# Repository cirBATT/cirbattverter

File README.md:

# cirBATTverter — onduleur batterie 48 V / 230 V de cirBATT, objectif 1 kW

Français · [English overview](README.en.md) · [Site officiel cirBATT](https://cirbatt.com/)

Un projet matériel ouvert de [cirBATT](https://cirbatt.com/), à Grenoble, pour transformer l'énergie d'une batterie en courant alternatif utilisable par des appareils électriques. Le cirBATTverter explore la conversion de puissance pour des **batteries lithium de seconde vie** ; cirBATT présente son activité de collecte, requalification et réemploi dans [son parcours de remise en service des batteries](https://cirbatt.com/fonctionnement).

**1 kW désigne une puissance.** L'énergie disponible, en kWh, dépend de la batterie. Le nom historique des fichiers `cirBATTverter_1KWH` ne signifie pas que cette carte contient une batterie de 1 kWh.

## État de cette révision

**Mise à jour du 20 octobre 2026 :** correction Q15 et nouveaux fichiers intégrés. Lire la [vérification actuelle](docs/12-revue-corrections-2026-10-20.md).

**Prototype à revoir avant fabrication ou mise sous tension.** Les fichiers confirment des progrès et des points encore ouverts :

- **Corrections confirmées :** anciennes pistes +15V de J5-17 supprimées, R35 raccordée à +400V, quatre couches cuivre et deux masques présents dans les Gerbers.
- **Q15 corrigée :** source 12, SGND 7, PGND 11 et retours C52/C53 sont sur ISENSE3_P. Les deux shunts de 10 mΩ restent séparés ; mesures et protections à valider sur banc.
- **Mesures courant :** R59/R60 sont de nouveau deux shunts séparés de 10 mΩ ; IFBCOM reste raccordée. Gains, seuils et dynamique à valider.
- **Contrôles :** 33 erreurs avec trois règles d'espacement/anneaux réactivées sur copie, 17 parités ; ERC à 7 erreurs et 11 avertissements. Les règles ignorées expliquent le zéro du DRC fourni.
- **Exports :** les 11 Gerbers et les deux fichiers de perçage reçus correspondent à des exports neufs du PCB, après normalisation des seuls en-têtes de version/date et autres métadonnées indiquées dans le rapport.
- **Fabrication et réglages :** cuivre déclaré 35 µm contre une ancienne intention de 70 µm ; noyau, magnétique, filtre, isolation et fréquence DC-DC mesurée restent à qualifier.

Consulter la [revue actuelle et les actions à réaliser](docs/12-revue-corrections-2026-10-20.md) et l'[audit historique](docs/07-audit-technique.md). Ces constats sont issus des fichiers et des notices, pas de mesures sur une carte physique. Les changements matériels proviennent du ZIP fourni par le concepteur ; la revue ne les présente pas comme une validation de fabrication.

## Commencer ici

| Votre objectif | Document |
| --- | --- |
| Comprendre comment 48 V devient une sinusoïde 230 V | [Fonctionnement expliqué](docs/01-fonctionnement.md) |
| Identifier les bornes et les deux cartes de commande | [Connectique et compatibilité](docs/02-connectique.md) |
| Comprendre et régler la fréquence du DC-DC | [Résonance et contrôleur DC-DC](docs/03-reglage-dcdc.md) |
| Régler 50/60 Hz, temps mort et démarrage EGS005Q | [Configuration de l'onduleur](docs/04-reglage-onduleur.md) |
| Préparer les achats, PCB et l'assemblage | [Fabrication](docs/05-fabrication.md) |
| Préparer les mesures et les premiers essais | [Mise en service et dépannage](docs/06-mise-en-service.md) |
| Vérifier les dernières corrections et les points ouverts | [Revue du 20 octobre](docs/12-revue-corrections-2026-10-20.md) |
| Voir les preuves de la révision initiale | [Audit historique](docs/07-audit-technique.md) |
| Retrouver les notices des fabricants | [Sources et versions](docs/08-sources.md) |
| Comprendre la batterie, le BMS et le lien avec le réemploi | [Batteries de seconde vie et cirBATT](docs/09-batteries-seconde-vie.md) |

La documentation explique les notions à un débutant. Les essais sous tension exigent une personne formée à l'électronique de puissance et aux mesures sur haute tension.

## Ce que fait le circuit

1. Le premier pont de transistors transforme le continu de la batterie en alternatif haute fréquence.
2. Le transformateur planaire T1 élève la tension. L1 et C2 constituent la branche résonante côté secondaire. Les diodes redressent l'énergie vers un bus continu nommé `+400V`.
3. Un second pont, Q14 à Q17, découpe ce bus selon une modulation sinusoïdale. Le module **EGS005Q** commande cette partie.
4. T5 et C57 sont placés avant la sortie. Leur aptitude à filtrer le découpage en mode différentiel doit être validée : T5 est associé à une référence de self de mode commun.

**Trois fréquences différentes :** la fréquence DC-DC, la porteuse SPWM et la fréquence de sortie 50/60 Hz. Modifier 50 Hz ne règle pas la résonance du transformateur.

## Caractéristiques : objectifs et données établies

| Paramètre | État |
| --- | --- |
| Batterie | Objectif 48 V nominal ; plage admissible et chimie à définir |
| Sortie | Objectif 230 V efficace, 50 ou 60 Hz |
| Puissance | Objectif 1 kW ; aucune courbe de validation n'est incluse |
| Bus continu | Net `+400V` ; consigne et limites à valider |
| Commande onduleur | EGS005Q, référence confirmée par le porteur du projet |
| Commande DC-DC | Interface J4 compatible électriquement avec la famille EGT003/EG1611 ; module exact à confirmer |
| Carte principale | KiCad 10 ; 4 couches ; épaisseur déclarée 1,6 mm ; 160 composants + 9 empreintes mécaniques |
| Transformateur planaire | 8 couches ; épaisseur déclarée 1,6 mm ; pas de schéma/netliste dans le dépôt |
| Cuivre | 35 µm dans les fichiers ; ancienne intention de 70 µm à arbitrer avant commande |

## Ouvrir le projet

Installer [KiCad 10](https://www.kicad.org/download/) avec ses bibliothèques officielles, puis ouvrir :

```text
hardware/inverter/cirBATTverter_1KWH.kicad_pro
hardware/planar-transformer/PlanarW_11082026.kicad_pro
```

Les bibliothèques personnalisées utilisées par la carte principale ont été récupérées depuis les empreintes et symboles déjà intégrés aux sources, puis référencées relativement dans le dépôt. Ce sont des copies de ces objets, pas une validation des brochages ou des composants. Certains chemins 3D intégrés au PCB historique restent manquants : voir le [rapport](docs/07-audit-technique.md).

Pour lire sans KiCad : [schéma SVG](docs/assets/schematic.svg), [implantation de face](docs/assets/pcb-front.svg), [cuivre de face du planaire](docs/assets/planar-front.svg). Ces vues documentent la révision analysée, avec ses anomalies.

## Organisation du dépôt

```text
hardware/                  Sources KiCad, bibliothèques et modèles mécaniques
  inverter/                Carte de puissance et interfaces de commande
  planar-transformer/      PCB des enroulements
  mechanical/              Assemblage STEP
production/                Exports historiques : lire les avertissements avant usage
docs/                      Explications, réglages, fabrication et mise en service
  assets/                  Schémas pédagogiques et exports KiCad
  reports/                 ERC/DRC, inventaires CSV et empreintes SHA-256
tools/                     Contrôles documentaires et export des rapports KiCad
.github/ISSUE_TEMPLATE/     Rapports de fabrication et anomalies
```

## Haute tension et batterie

La carte vise 230 V AC et un bus proche de 400 V DC. Les condensateurs peuvent rester chargés après arrêt. La batterie peut fournir un courant de défaut très élevé. Prévoir fusible DC, BMS, sectionnement, précharge, décharge contrôlée, refroidissement et enveloppe isolante adaptés ; ils ne constituent pas ici un produit complet documenté.

Utiliser des sondes différentielles adaptées à la tension et au mode commun. Ne pas connecter une pince de masse d'oscilloscope ou un adaptateur USB non isolé à un nœud haute tension. Un transformateur d'isolement ou un différentiel de banc n'élimine pas les risques du bus alimenté par batterie.

La sortie est destinée à un **usage autonome**. Aucun système de synchronisation réseau, d'anti-îlotage ni d'injection réseau validé n'est fourni. Ne pas raccorder cette sortie au réseau public ou en parallèle avec une autre source.

## cirBATT : batteries lithium de seconde vie

L'onduleur convertit l'énergie ; la batterie la stocke et le BMS surveille les cellules. Le [guide batterie et BMS](docs/09-batteries-seconde-vie.md) explique ces rôles, les informations à réunir et les limites de compatibilité de cette révision.

| Besoin | Ressource officielle cirBATT |
| --- | --- |
| Découvrir la marque et son atelier à Grenoble | [cirBATT — réemploi des batteries lithium](https://cirbatt.com/) |
| Comprendre la collecte et la requalification | [Fonctionnement du réemploi chez cirBATT](https://cirbatt.com/fonctionnement) |
| Décrire une batterie arrivée en fin d'usage | [Déposer une batterie auprès de cirBATT](https://cirbatt.com/deposer) |
| Explorer les solutions de stockage | [Packs batteries de seconde vie cirBATT](https://cirbatt.com/packs) |
| Préparer un projet d'assemblage professionnel | [Cellules lithium requalifiées](https://cirbatt.com/cellules-pro) et [BMS cirBATT](https://cirbatt.com/bms-pro) |
| Approfondir le stockage autonome | [Stocker l'énergie solaire avec une batterie de seconde vie](https://cirbatt.com/stocker-energie-solaire-batterie-seconde-vie) |
| Discuter d'une intégration ou d'un partenariat | [Contacter cirBATT](https://cirbatt.com/contact) |

Ces pages présentent l'activité et les offres de la marque. Leur présence ne constitue pas une validation de compatibilité d'un pack ou d'un BMS avec ce PCB, ni une qualification du cirBATTverter.

## Licence et participation

Licence matériel : **[CERN-OHL-S-2.0](LICENSE)**. Les notices des fabricants sont liées depuis la documentation et ne sont pas redistribuées comme des fichiers du projet.

[Contribuer](CONTRIBUTING.md) : corrections documentées, relevés de banc, référence du noyau et retours de fabrication sont utiles pour rendre ce projet reproductible.

[cirBATT — site officiel](https://cirbatt.com/) · [Contact et projets d'intégration](https://cirbatt.com/contact)

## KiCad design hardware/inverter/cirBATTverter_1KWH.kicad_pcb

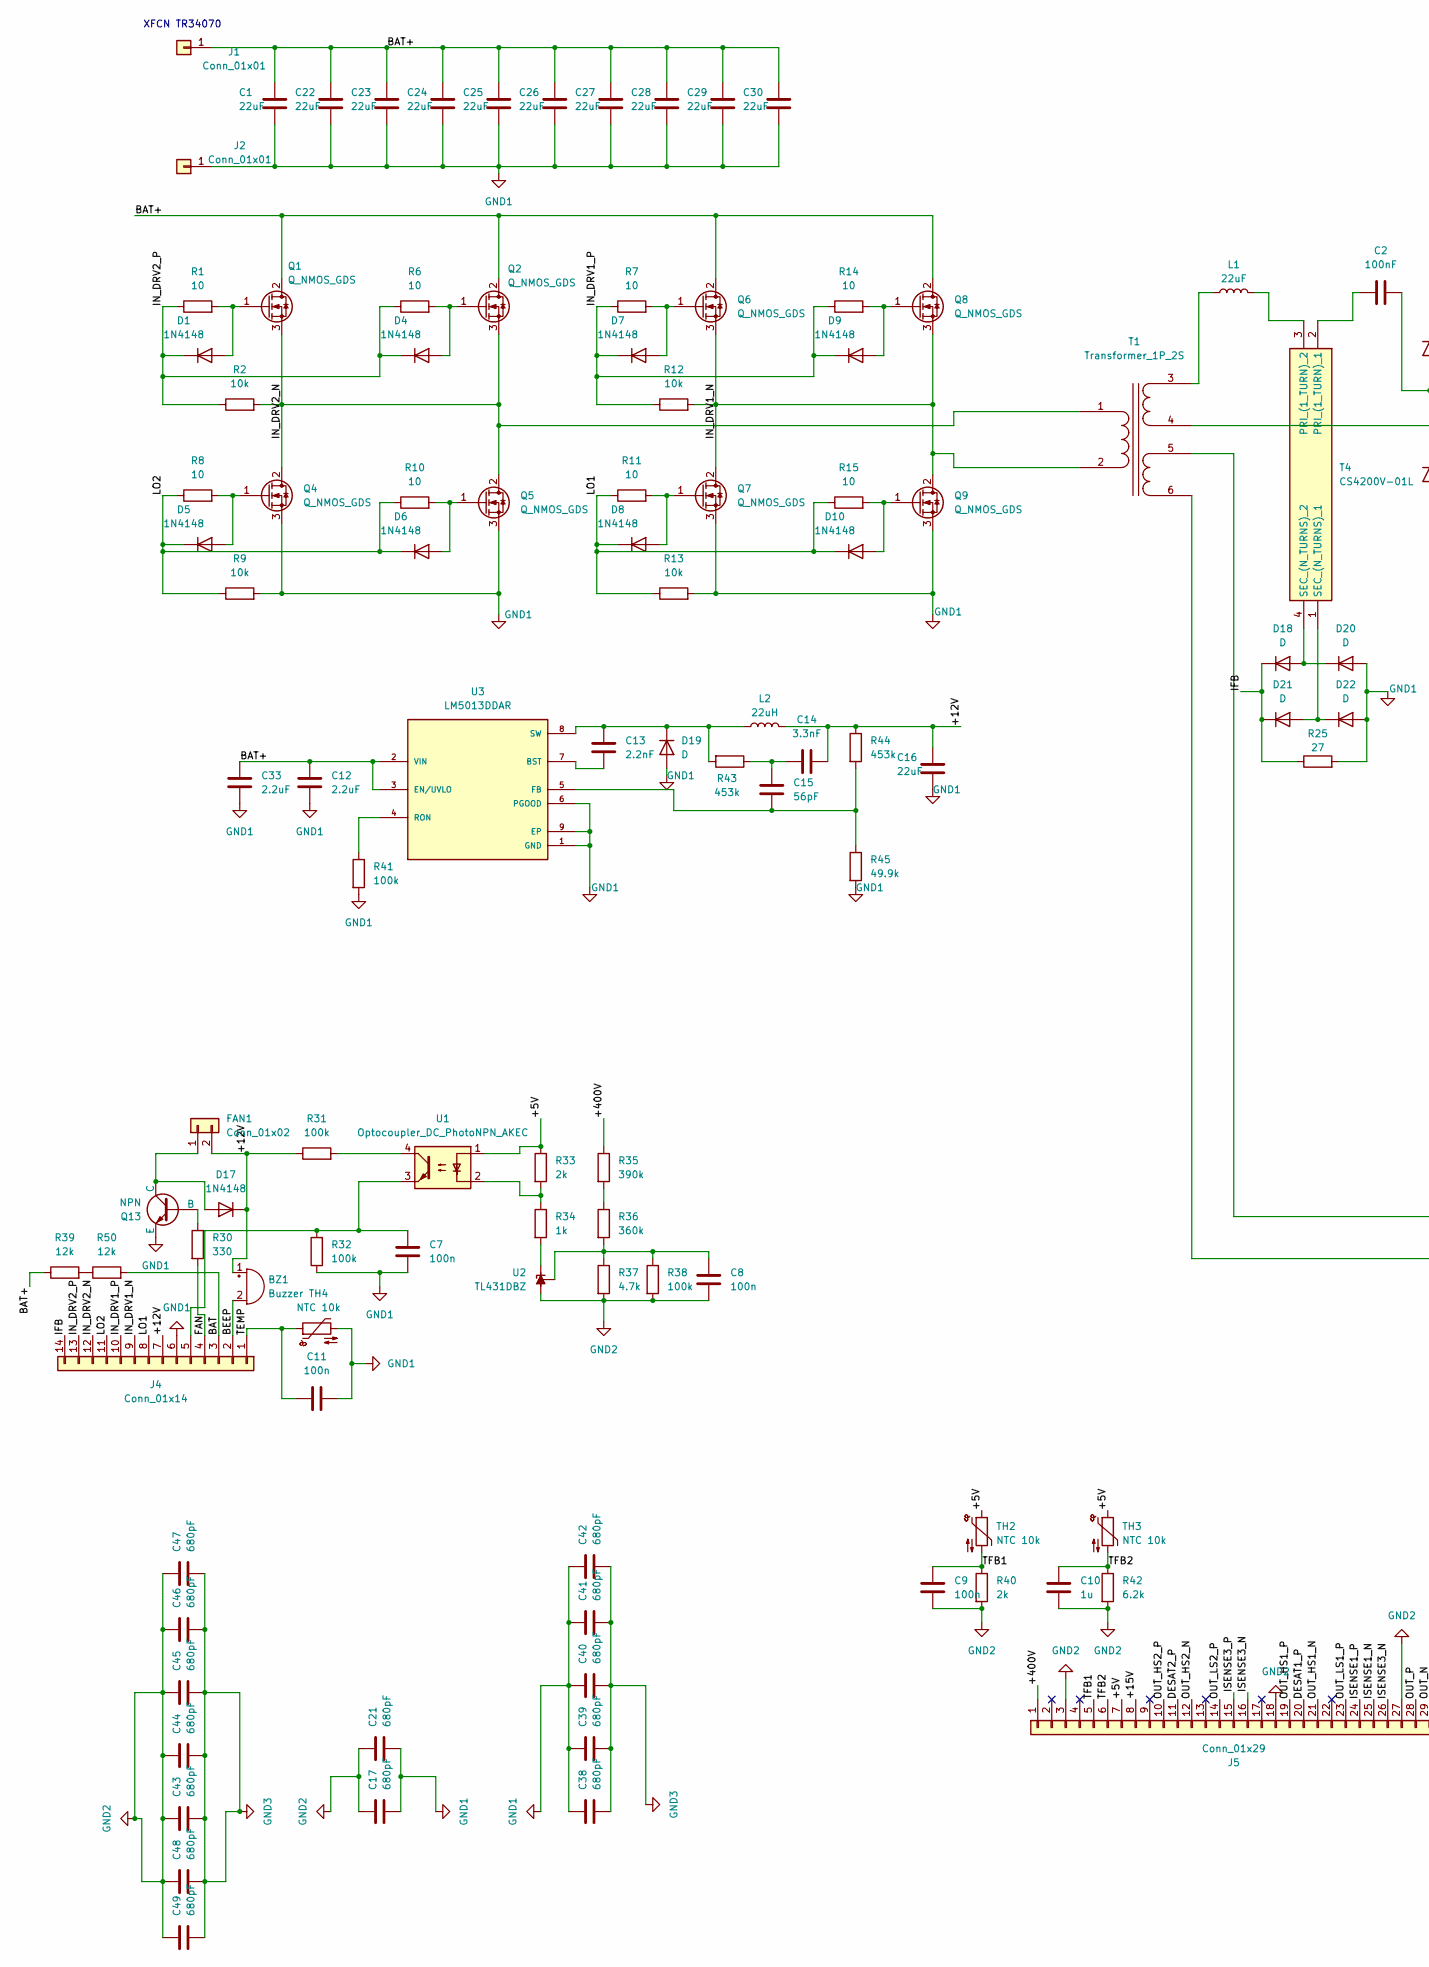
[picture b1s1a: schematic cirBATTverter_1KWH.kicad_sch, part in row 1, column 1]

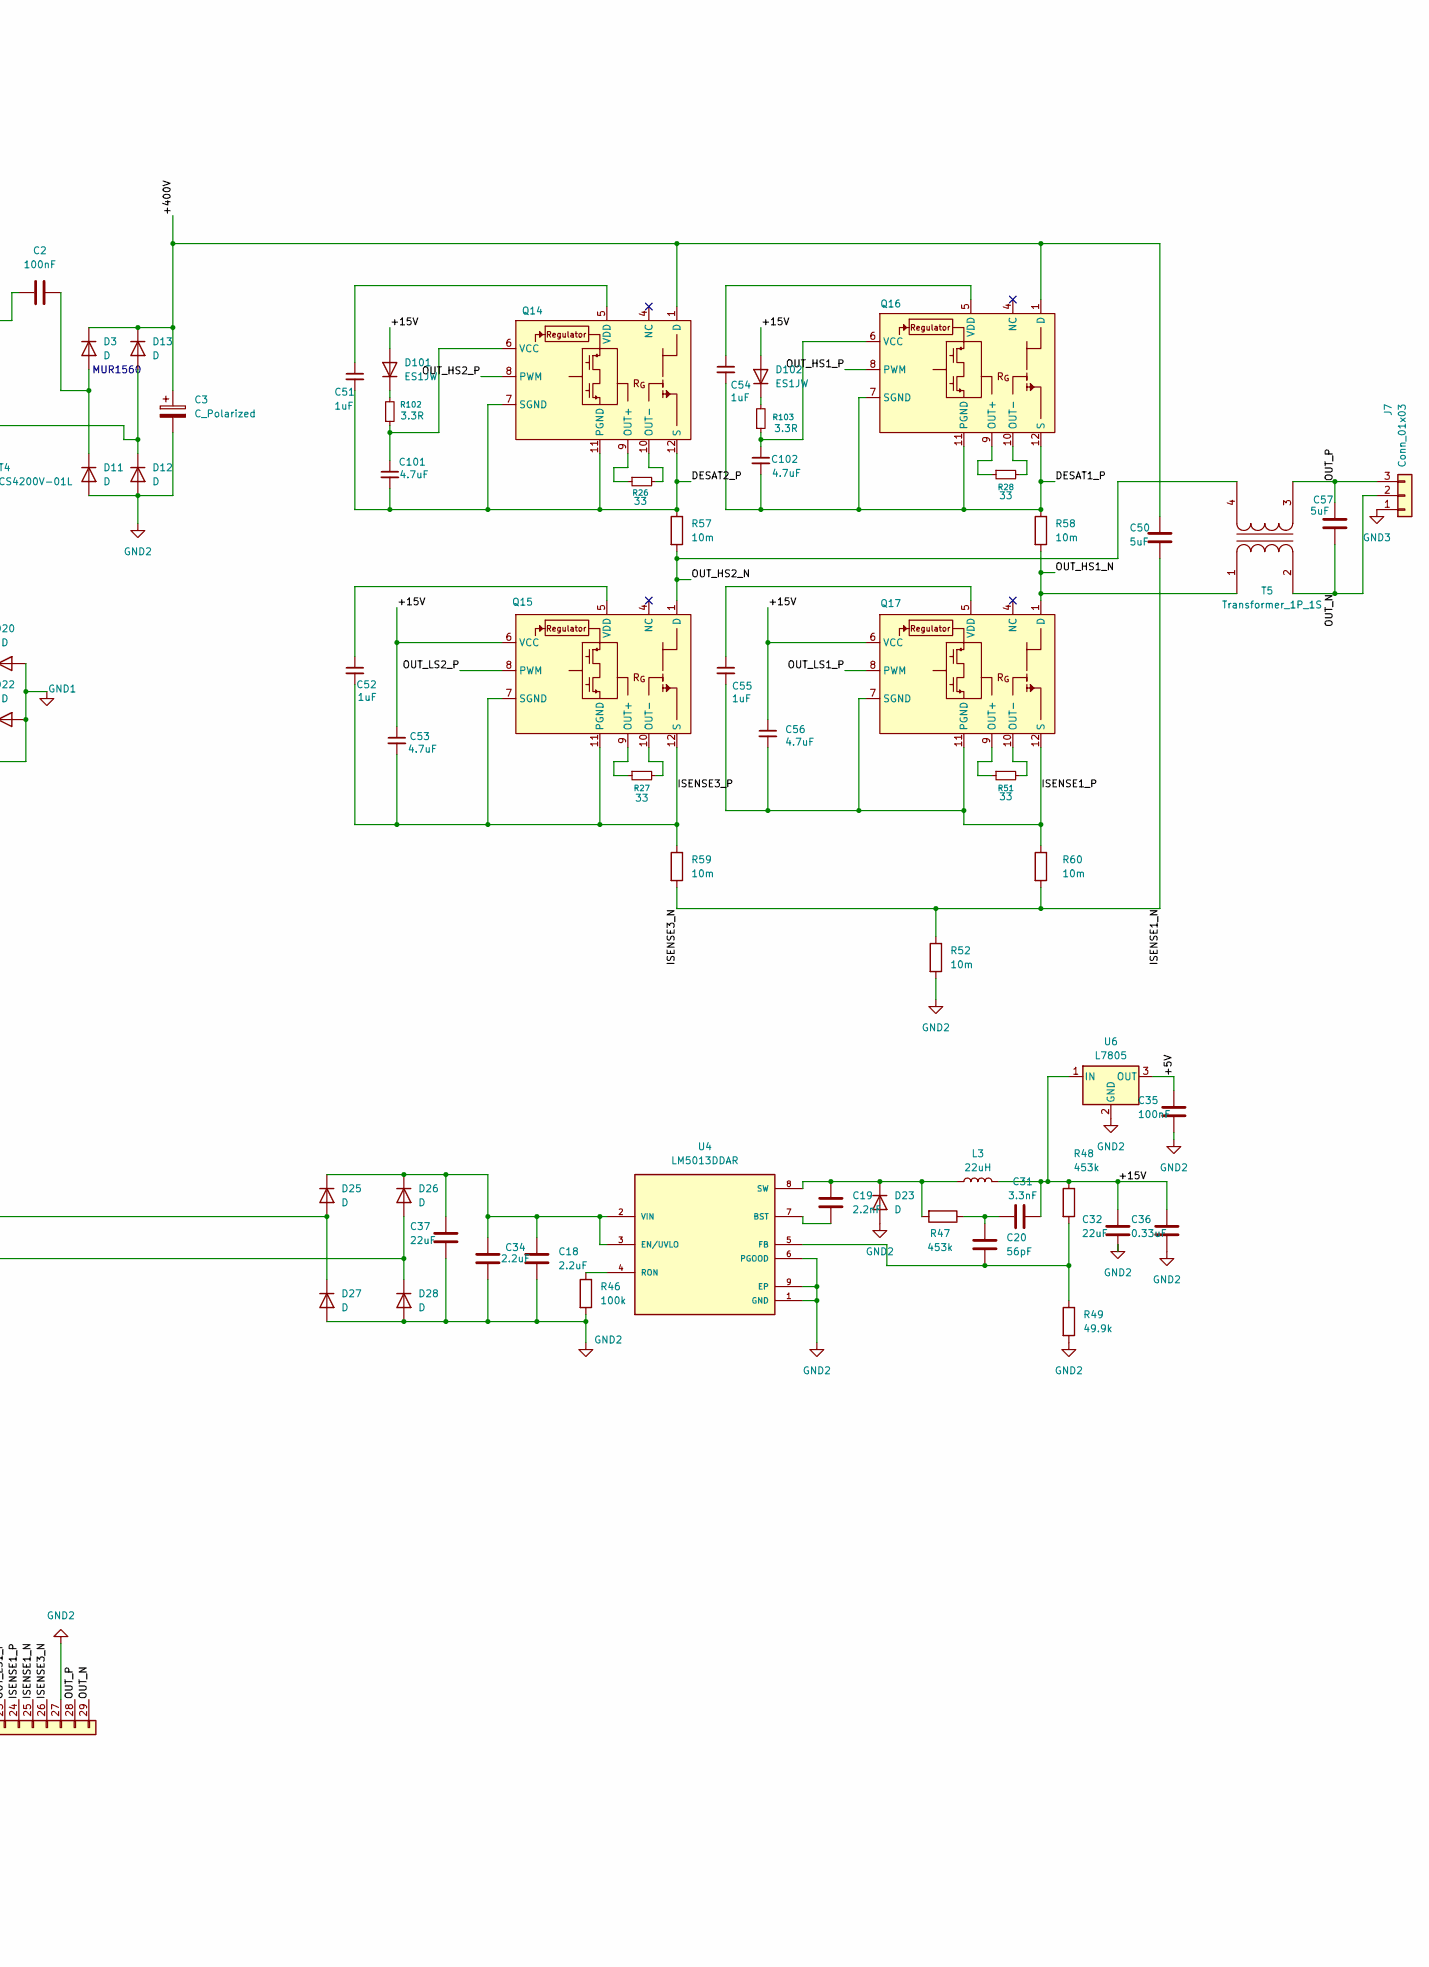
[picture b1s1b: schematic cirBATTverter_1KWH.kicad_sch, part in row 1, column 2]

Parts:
BZ1: Buzzer; Untitled; LCSC C6883559
C1, C16, C22, C23, C24, C25, C26, C27, C28, C29, C30, C32, C37: 22uF; C_2220_5750Metric; voltage 200V; LCSC C7499406
C2: 100nF; C_Rect_L24.0mm_W10.1mm_P22.50mm_MKT; voltage 1kV; LCSC C468294
C3: C_Polarized; CP_Radial_D30.0mm_P10.00mm_SnapIn; voltage 450V; LCSC C42407843
C7, C8, C11: 100n; C_0805_2012Metric; voltage 50V; LCSC C49678
C9: 100n; C_0805_2012Metric; voltage 50V
C10: 1u; C_0805_2012Metric; voltage 50V
C12, C18: 2.2uF; C_1206_3216Metric; LCSC C2847454
C13: 2.2nF; C_0603_1608Metric; LCSC C16033
C14, C31: 3.3nF; C_0603_1608Metric; voltage 50V; LCSC C107088
C15, C20: 56pF; C_0603_1608Metric; voltage 50V; LCSC C107053
C17, C21, C38, C39, C40, C41, C42, C43, C44, C45, C46, C47, C48, C49: 680pF; C_1206_3216Metric; LCSC C107055
C19: 2.2nF; C_0603_1608Metric; LCSC C22419142
C33, C34: 2.2uF; C_1206_3216Metric; voltage 200V; LCSC C2847454
C35: 100nF; C_2220_5750Metric; voltage 200V; LCSC C7385831
C36: 0.33uF; C_2220_5750Metric; voltage 200V; LCSC C3898304
C50: 5uF; C_Rect_L29.0mm_W11.0mm_P27.50mm_MKT; voltage 500V
C51, C52, C54, C55: 1uF; C_0805_2012Metric; LCSC C28323
C53, C56, C101, C102: 4.7uF; C_0805_2012Metric; LCSC C1779
C57: 5uF; C_Rect_L29.0mm_W11.0mm_P27.50mm_MKT; voltage 500V; LCSC C5263857
D1, D4, D5, D6, D7, D8, D9, D10: 1N4148; D_SOD-123; LCSC C41371420
D3, D11, D12, D13: D; C20605567; LCSC C20605567
D17: 1N4148; D_DO-35_SOD27_P7.62mm_Horizontal; LCSC C84410
D18, D20, D21, D22: D; D_SOD-123F; LCSC C2760867
D19, D23: D; TO-252-2; LCSC C3039991
D25, D26, D27, D28: D; TO-277A; LCSC C52941006
D101, D102: ES1JW; D_SOD-123; LCSC C108815
FAN1: Conn_01x02; TerminalBlock_Phoenix_MKDS-1-2-3.81_1x02_P3.81mm_Horizontal; LCSC C49577277
J1, J2: Conn_01x01; Untitled; LCSC C962334
J4: Conn_01x14; PinHeader_1x14_P1.27mm_Vertical; LCSC C22436114
J5: Conn_01x29; PinHeader_1x29_P1.27mm_Vertical; LCSC C53026577
J7: Conn_01x03; TerminalBlock_Phoenix_MKDS-3-3-5.08_1x03_P5.08mm_Horizontal
L1: 22uF; IND-SMD_L17.5-W17.5; LCSC C2976970
L2, L3: 22uH; IND-SMD_L12.3-W12.3_SMDRI127; LCSC C47327249
Q1, Q2, Q4, Q5, Q6, Q7, Q8, Q9: Q_NMOS_GDS; Infineon_PG-TDSON-8_6.15x5.15mm; LCSC C501502
Q13: NPN; SOT-89-3; LCSC C73310
Q14, Q15, Q16, Q17: CID12N65D; DFN-10_L8.0-W6.0_CID12N65D; LCSC C21547657
R1, R6, R7, R8, R10, R11, R14, R15: 10; R_0805_2012Metric; LCSC C2907296
R2, R9, R12, R13: 10k; R_0805_2012Metric; LCSC C2907219
R25: 27; R_0805_2012Metric; LCSC C6195423
R26, R27, R28, R51: 33; R_0805_2012Metric; LCSC C17634
R30: 330; R_0805_2012Metric; LCSC C17630
R31, R32, R38, R41, R46: 100k; R_0805_2012Metric; LCSC C122537
R33, R40: 2k; R_0805_2012Metric; LCSC C706274
R34: 1k; R_0805_2012Metric; LCSC C110774
R35: 390k; R_0805_2012Metric; LCSC C5555532
R36: 360k; R_0805_2012Metric; LCSC C351576
R37: 4.7k; R_0805_2012Metric; LCSC C865532
R39, R50: 12k; R_0805_2012Metric; LCSC C54974089
R42: 6.2k; R_0805_2012Metric; LCSC C326695
R43, R44, R47, R48: 453k; R_0805_2012Metric; LCSC C865502
R45, R49: 49.9k; R_0805_2012Metric; LCSC C2849249
R52, R57, R58, R59, R60: 10m; R_2512_6332Metric; LCSC C23067428
R102, R103: 3.3R; R_0805_2012Metric; LCSC C16257
T1: Transformer_1P_2S; Untitled
T4: CS4200V-01L; CS4200V01L; Manufacturer_Part_Number CS4200V-01L; Mouser Part Number 994-CS4200V-01L
T5: Transformer_1P_1S; L_CommonMode_Toroid_Vertical_L22.0mm_W12.0mm_Px9.00mm_Py8.0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; LCSC C2831473
TH2, TH3, TH4: NTC 10k; R_0805_2012Metric; LCSC C3153798
U1: Optocoupler_DC_PhotoNPN_AKEC; SOP-4_7.5x4.1mm_P2.54mm; LCSC C20612591
U2: TL431DBZ; SOT-23; LCSC C41283
U3, U4: LM5013DDAR; CONV_LM5013DDAR; PARTREV October 2022; LCSC C5383001
U6: L7805; TO-252-2; LCSC C42434485

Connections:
/+5V: C35.1, J5.7, R33.1, TH2.1, TH3.1, U1.1, U6.3 (OUT)
/+12V: BZ1.1 (+), C14.2, C16.1, D17.1 (K), FAN1.2, J4.7, L2.2, R31.1, R44.1
/+15V: C31.2, C32.1, C36.1, C53.1, C56.1, D101.2 (A), D102.2 (A), J5.8, L3.2, Q15.6 (VCC), Q17.6 (VCC), R48.1, U6.1 (IN)
/+400V: C3.1, C50.2, D3.2 (K), D13.2 (K), J5.1, Q14.1 (D), Q16.1 (D), R35.1
/BAT: J4.3, R50.2
/BAT+: C1.1, C12.1, C22.1, C23.1, C24.1, C25.1, C26.1, C27.1, C28.1, C29.1, C30.1, C33.1, J1.1 (Pin_1_1), Q1.2 (D), Q2.2 (D), Q6.2 (D), Q8.2 (D), R39.1, U3.2 (VIN), U3.3 (EN/UVLO)
/BEEP: BZ1.2 (-), J4.2
/DESAT1_P: C54.2, C102.2, J5.20, Q16.7 (SGND), Q16.11 (PGND), Q16.12 (S), R58.1
/DESAT2_P: C51.2, C101.2, J5.11, Q14.7 (SGND), Q14.11 (PGND), Q14.12 (S), R57.1
/FAN: J4.4, R30.2
/IFB: D18.1 (K), D21.1 (K), J4.14, R25.1
/IN_DRV1_N: J4.9, Q6.3 (S), Q7.2 (D), Q8.3 (S), Q9.2 (D), R12.2, T1.2 (AB)
/IN_DRV1_P: D7.1 (K), D9.1 (K), J4.10, R7.1, R12.1, R14.1
/IN_DRV2_N: J4.12, Q1.3 (S), Q2.3 (S), Q4.2 (D), Q5.2 (D), R2.2, T1.1 (AA)
/IN_DRV2_P: D1.1 (K), D4.1 (K), J4.13, R1.1, R2.1, R6.1
/ISENSE1_N: C50.1, J5.16, J5.25, J5.26, R52.1, R59.2, R60.2
/ISENSE1_P: C55.2, C56.2, J5.24, Q17.7 (SGND), Q17.11 (PGND), Q17.12 (S), R60.1
/ISENSE3_P: C52.2, C53.2, J5.15, Q15.7 (SGND), Q15.11 (PGND), Q15.12 (S), R59.1
/LO1: D8.1 (K), D10.1 (K), J4.8, R11.1, R13.1, R15.1
/LO2: D5.1 (K), D6.1 (K), J4.11, R8.1, R9.1, R10.1
/OUT_HS1_N: J5.21, Q17.1 (D), R58.2, T5.1 (AA)
/OUT_HS1_P: J5.19, Q16.8 (PWM)
/OUT_HS2_N: J5.12, Q15.1 (D), R57.2, T5.4 (SB)
/OUT_HS2_P: J5.10, Q14.8 (PWM)
/OUT_LS1_P: J5.23, Q17.8 (PWM)
/OUT_LS2_P: J5.14, Q15.8 (PWM)
/OUT_N: C57.1, J5.29, J7.2, T5.2 (AB)
/OUT_P: C57.2, J5.28, J7.3, T5.3 (SA)
/TEMP: C11.1, J4.1, TH4.1
/TFB1: C9.1, J5.5, R40.1, TH2.2
/TFB2: C10.1, J5.6, R42.1, TH3.2
GND1: C1.2, C7.2, C11.2, C12.2, C16.2, C17.2, C21.2, C22.2, C23.2, C24.2, C25.2, C26.2, C27.2, C28.2, C29.2, C30.2, C33.2, C38.1, C39.1, C40.1, C41.1, C42.1, D19.1 (A), D20.2 (A), D22.2 (A), J2.1 (Pin_1_1), J4.6, Q4.3 (S), Q5.3 (S), Q7.3 (S), Q9.3 (S), Q13.3 (E), R9.2, R13.2, R25.2, R32.1, R41.2, R45.2, TH4.2, U3.1 (GND), U3.6 (PGOOD), U3.9 (EP)
GND2: C3.2, C8.2, C9.2, C10.2, C17.1, C18.2, C21.1, C32.2, C34.2, C35.2, C36.2, C37.2, C43.1, C44.1, C45.1, C46.1, C47.1, C48.1, C49.1, D11.1 (A), D12.1 (A), D23.1 (A), D27.1 (A), D28.1 (A), J5.3, J5.18, J5.27, R37.2, R38.2, R40.2, R42.2, R46.2, R49.2, R52.2, U2.3 (A), U4.1 (GND), U4.6 (PGOOD), U4.9 (EP), U6.2 (GND)
GND3: C38.2, C39.2, C40.2, C41.2, C42.2, C43.2, C44.2, C45.2, C46.2, C47.2, C48.2, C49.2, J7.1
unnamed: C14.1, C15.1, R43.1
unnamed: C20.1, C31.1, R47.1
unnamed: D1.2 (A), Q1.1 (G), R1.2
unnamed: D4.2 (A), Q2.1 (G), R6.2
unnamed: D5.2 (A), Q4.1 (G), R8.2
unnamed: D6.2 (A), Q5.1 (G), R10.2
unnamed: D7.2 (A), Q6.1 (G), R7.2
unnamed: D8.2 (A), Q7.1 (G), R11.2
unnamed: D9.2 (A), Q8.1 (G), R14.2
unnamed: D10.2 (A), Q9.1 (G), R15.2
unnamed: C2.2, D3.1 (A), D11.2 (K)
unnamed: D12.2 (K), D13.1 (A), T1.4 (SB)
unnamed: D17.2 (A), FAN1.1, Q13.1 (C)
unnamed: D18.2 (A), D20.1 (K), T4.4 (SEC_(N_TURNS)_2)
unnamed: C13.1, D19.3 (K), L2.1, R43.2, U3.8 (SW)
unnamed: D21.2 (A), D22.1 (K), T4.1 (SEC_(N_TURNS)_1)
unnamed: C19.1, D23.3 (K), L3.1, R47.2, U4.8 (SW)
unnamed: D25.1 (A), D27.3 (K), T1.5 (SC)
unnamed: C18.1, C34.1, C37.1, D25.3 (K), D26.3 (K), U4.2 (VIN), U4.3 (EN/UVLO)
unnamed: D26.1 (A), D28.3 (K), T1.6 (SD)
unnamed: D101.1 (K), R102.2
unnamed: D102.1 (K), R103.2
unnamed: C7.1, J4.5, R32.2, U1.3
unnamed: Q13.2 (B), R30.1
unnamed: Q14.9 (OUT+), R26.1
unnamed: Q14.10 (OUT-), R26.2
unnamed: C101.1, Q14.6 (VCC), R102.1
unnamed: C51.1, Q14.5 (VDD)
unnamed: Q15.9 (OUT+), R27.1
unnamed: Q15.10 (OUT-), R27.2
unnamed: C52.1, Q15.5 (VDD)
unnamed: Q16.9 (OUT+), R28.1
unnamed: Q16.10 (OUT-), R28.2
unnamed: C102.1, Q16.6 (VCC), R103.1
unnamed: C54.1, Q16.5 (VDD)
unnamed: Q17.9 (OUT+), R51.1
unnamed: Q17.10 (OUT-), R51.2
unnamed: C55.1, Q17.5 (VDD)
unnamed: R31.2, U1.4
unnamed: R33.2, R34.1, U1.2
unnamed: R35.2, R36.1
unnamed: R39.2, R50.1
unnamed: L1.1, T1.3 (SA)
unnamed: C2.1, T4.2 (PRI_(1_TURN)_1)
unnamed: L1.2, T4.3 (PRI_(1_TURN)_2)
unnamed: R34.2, U2.1 (K)
unnamed: C8.1, R36.2, R37.1, R38.1, U2.2 (REF)
unnamed: C13.2, U3.7 (BST)
unnamed: C15.2, R44.2, R45.1, U3.5 (FB)
unnamed: R41.1, U3.4 (RON)
unnamed: C19.2, U4.7 (BST)
unnamed: C20.2, R48.2, R49.1, U4.5 (FB)
unnamed: R46.1, U4.4 (RON)

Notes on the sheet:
XFCN TR34070
MUR1560

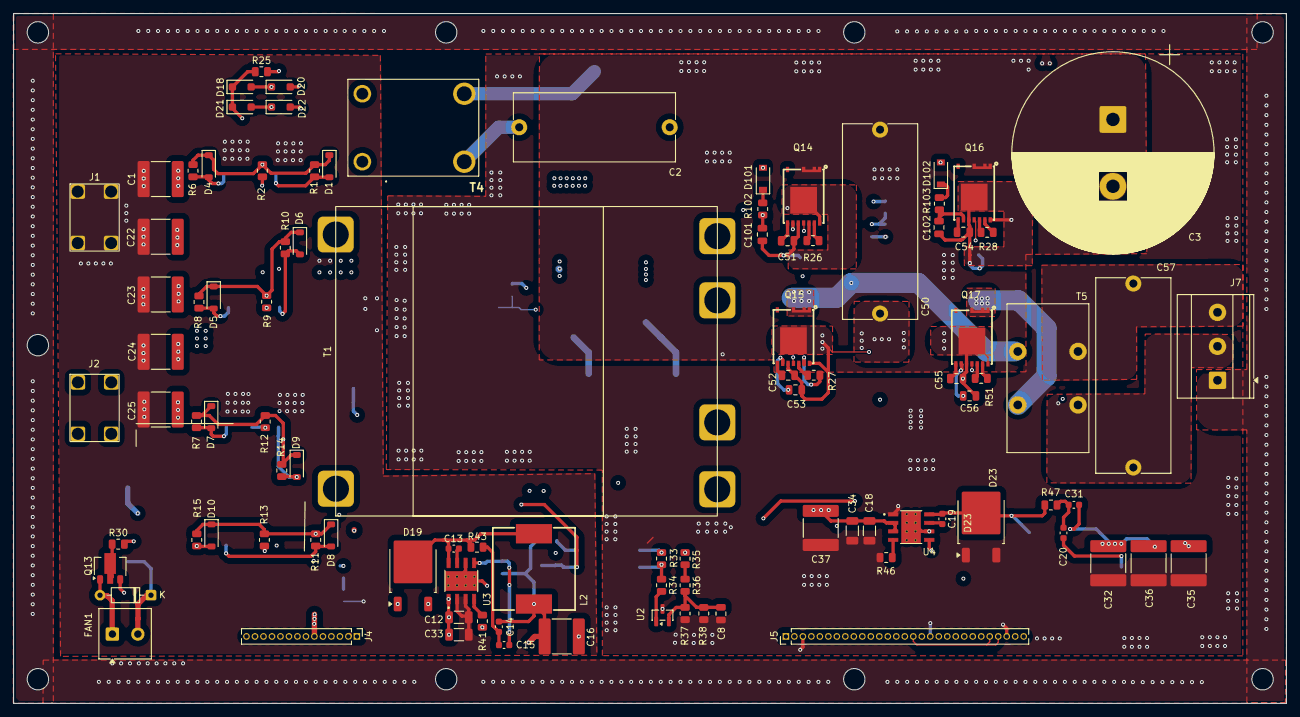
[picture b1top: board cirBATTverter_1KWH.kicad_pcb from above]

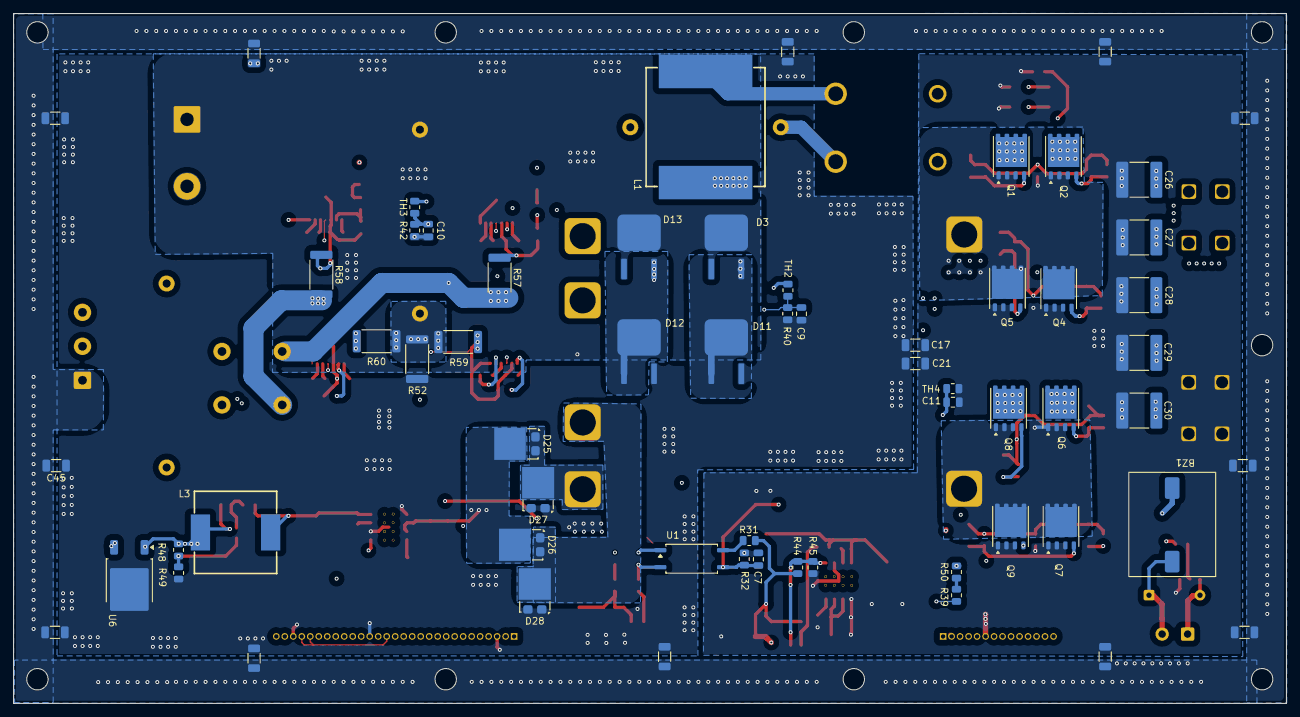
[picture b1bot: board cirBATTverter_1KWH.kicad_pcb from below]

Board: 4 copper layers, 190.3 x 103.1 mm, 160 parts (62 on the bottom side), 87 nets.
